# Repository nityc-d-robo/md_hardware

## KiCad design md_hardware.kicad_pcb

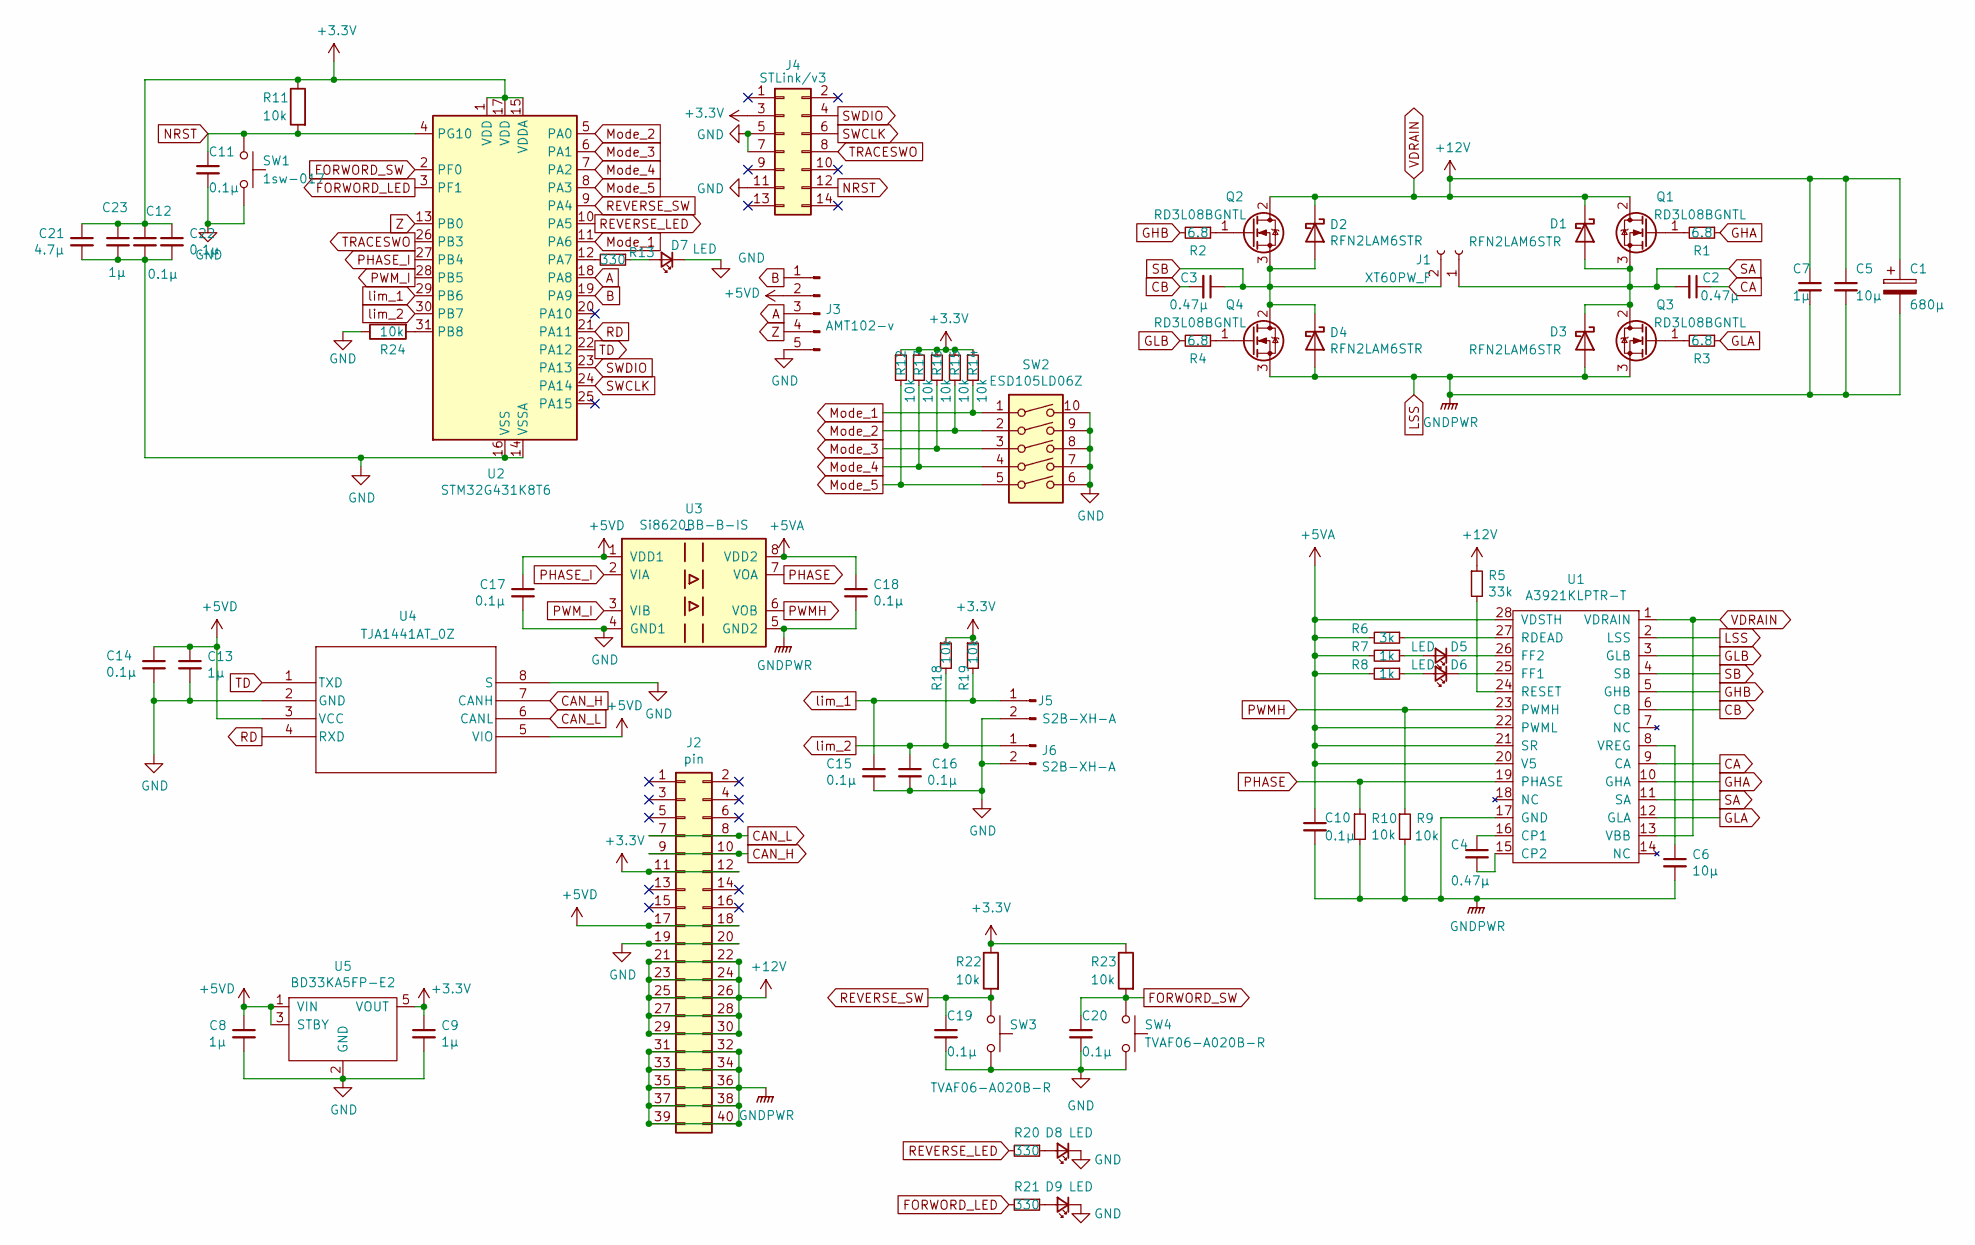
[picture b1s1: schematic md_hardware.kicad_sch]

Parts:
C1: 680µ; CP_Elec_10x12.6
C2, C3, C4: 0.47μ; C_0603_1608Metric_Pad1.08x0.95mm_HandSolder
C5, C6: 10μ; C_0603_1608Metric_Pad1.08x0.95mm_HandSolder
C7, C8, C9, C13, C23: 1μ; C_0603_1608Metric_Pad1.08x0.95mm_HandSolder
C10, C11, C12, C14, C15, C16, C17, C18, C19, C20, C22: 0.1μ; C_0603_1608Metric_Pad1.08x0.95mm_HandSolder
C21: 4.7μ; C_0603_1608Metric_Pad1.08x0.95mm_HandSolder
D1, D2, D3, D4: RFN2LAM6STR; D_SOD-128
D5, D6, D7, D8, D9: LED; LED_0603_1608Metric_Pad1.05x0.95mm_HandSolder
J1: XT60PW_F; XT60PW-F
J2: pin; PinHeader_2x20_P2.54mm_Horizontal
J3: AMT102-v; JST_XH_S5B-XH-A_1x05_P2.50mm_Horizontal
J4: STLink/v3; CONN14_3220-14_CNC
J5, J6: S2B-XH-A; JST_XH_S2B-XH-A_1x02_P2.50mm_Horizontal
Q1, Q2, Q3, Q4: RD3L08BGNTL; TO-252-2
R1, R2, R3, R4: 6.8; R_0603_1608Metric_Pad0.98x0.95mm_HandSolder
R5: 33k; R_0603_1608Metric_Pad0.98x0.95mm_HandSolder
R6: 3k; R_0603_1608Metric_Pad0.98x0.95mm_HandSolder
R7, R8: 1k; R_0603_1608Metric_Pad0.98x0.95mm_HandSolder
R9, R10, R11, R12, R14, R15, R16, R17, R18, R19, R22, R23, R24: 10k; R_0603_1608Metric_Pad0.98x0.95mm_HandSolder
R13, R20, R21: 330; R_0603_1608Metric_Pad0.98x0.95mm_HandSolder
SW1: 1sw-017; TVAF06-A020B-R
SW2: ESD105LD06Z; SW_DIP_SPSTx05_Slide_ESD105LD06Z_P2.54mm
SW3, SW4: TVAF06-A020B-R
U1: A3921KLPTR-T; TSSOP-28_4.4x9.7mm_P0.65mm
U2: STM32G431K8T6; LQFP-32_7x7mm_P0.8mm
U3: Si8620BB-B-IS; SOIC-8_3.9x4.9mm_P1.27mm
U4: TJA1441AT_0Z; SO8_SOT96-1_NXP
U5: BD33KA5FP-E2; SOT-23-5

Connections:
+3.3V: C9.1, C12.1, C21.1, C22.1, C23.1, J2.11, J2.12, J4.3, R11.1, R12.1, R14.1, R15.1, R16.1, R17.1, R18.1, R19.1, R22.1, R23.1, U2.1 (VDD), U2.15 (VDDA), U2.17 (VDD), U5.5 (VOUT)
+5VA: C10.1, C18.1, R6.2, R7.2, R8.2, U1.20 (V5), U1.21 (SR), U1.22 (PWML), U1.28 (VDSTH), U3.8 (VDD2)
+5VD: C8.1, C13.1, C14.1, C17.1, J2.17, J2.18, J3.2, U3.1 (VDD1), U4.3 (VCC), U4.5 (VIO), U5.1 (VIN), U5.3 (STBY)
A: J3.3, U2.18 (PA8)
B: J3.1, U2.19 (PA9)
CA: C2.1, U1.9 (CA)
CAN_H: J2.9, J2.10, U4.7 (CANH)
CAN_L: J2.7, J2.8, U4.6 (CANL)
CB: C3.2, U1.6 (CB)
FORWORD_LED: R21.2, U2.3 (PF1)
FORWORD_SW: C20.1, R23.2, SW4.1, U2.2 (PF0)
GHA: R1.1, U1.10 (GHA)
GHB: R2.2, U1.5 (GHB)
GLA: R3.1, U1.12 (GLA)
GLB: R4.2, U1.3 (GLB)
GND: C8.2, C9.2, C11.2, C12.2, C13.2, C14.2, C15.2, C16.2, C17.2, C19.2, C20.2, C21.2, C22.2, C23.2, D7.1 (K), D8.1 (K), D9.1 (K), J2.19, J2.20, J3.5, J4.5, J4.7, J4.11, J5.2, J6.2, R24.1, SW1.2, SW2.6, SW2.7, SW2.8, SW2.9, SW2.10, SW3.2, SW4.2, U2.14 (VSSA), U2.16 (VSS), U2.32 (VSS), U3.4 (GND1), U4.2 (GND), U4.8 (S), U5.2 (GND)
LSS: C1.2, C5.2, C6.2, C7.2, C10.2, C18.2, D3.2 (A), D4.2 (A), J2.31, J2.32, J2.33, J2.34, J2.35, J2.36, J2.37, J2.38, J2.39, J2.40, Q3.3 (S), Q4.3 (S), R9.2, R10.2, U1.2 (LSS), U1.17 (GND), U3.5 (GND2)
Mode_1: R14.2, SW2.1, U2.11 (PA6)
Mode_2: R15.2, SW2.2, U2.5 (PA0)
Mode_3: R16.2, SW2.3, U2.6 (PA1)
Mode_4: R17.2, SW2.4, U2.7 (PA2)
Mode_5: R12.2, SW2.5, U2.8 (PA3)
NRST: C11.1, J4.12, R11.2, SW1.1, U2.4 (PG10)
unnamed: D5.2 (A), R7.1
unnamed: D5.1 (K), U1.26 (FF2)
unnamed: D6.2 (A), R8.1
unnamed: D6.1 (K), U1.25 (FF1)
unnamed: D7.2 (A), R13.1
unnamed: D8.2 (A), R20.1
unnamed: D9.2 (A), R21.1
unnamed: Q1.1 (G), R1.2
unnamed: Q2.1 (G), R2.1
unnamed: Q3.1 (G), R3.2
unnamed: Q4.1 (G), R4.1
unnamed: C4.1, U1.16 (CP1)
unnamed: C4.2, U1.15 (CP2)
unnamed: R6.1, U1.27 (RDEAD)
unnamed: R5.2, U1.24 (RESET)
unnamed: C6.1, U1.8 (VREG)
unnamed: R13.2, U2.12 (PA7)
unnamed: R24.2, U2.31 (PB8)
PHASE: R10.1, U1.19 (PHASE), U3.7 (VOA)
PHASE_I: U2.27 (PB4), U3.2 (VIA)
PWMH: R9.1, U1.23 (PWMH), U3.6 (VOB)
PWM_I: U2.28 (PB5), U3.3 (VIB)
RD: U2.21 (PA11), U4.4 (RXD)
REVERSE_LED: R20.2, U2.10 (PA5)
REVERSE_SW: C19.1, R22.2, SW3.1, U2.9 (PA4)
SA: C2.2, D1.2 (A), D3.1 (K), J1.1, Q1.3 (S), Q3.2 (D), U1.11 (SA)
SB: C3.1, D2.2 (A), D4.1 (K), J1.2, Q2.3 (S), Q4.2 (D), U1.4 (SB)
SWCLK: J4.6, U2.24 (PA14)
SWDIO: J4.4, U2.23 (PA13)
TD: U2.22 (PA12), U4.1 (TXD)
TRACESWO: J4.8, U2.26 (PB3)
VDRAIN: C1.1, C5.1, C7.1, D1.1 (K), D2.1 (K), J2.21, J2.22, J2.23, J2.24, J2.25, J2.26, J2.27, J2.28, J2.29, J2.30, Q1.2 (D), Q2.2 (D), R5.1, U1.1 (VDRAIN), U1.13 (VBB)
Z: J3.4, U2.13 (PB0)
lim_1: C15.1, J5.1, R19.2, U2.29 (PB6)
lim_2: C16.1, J6.1, R18.2, U2.30 (PB7)

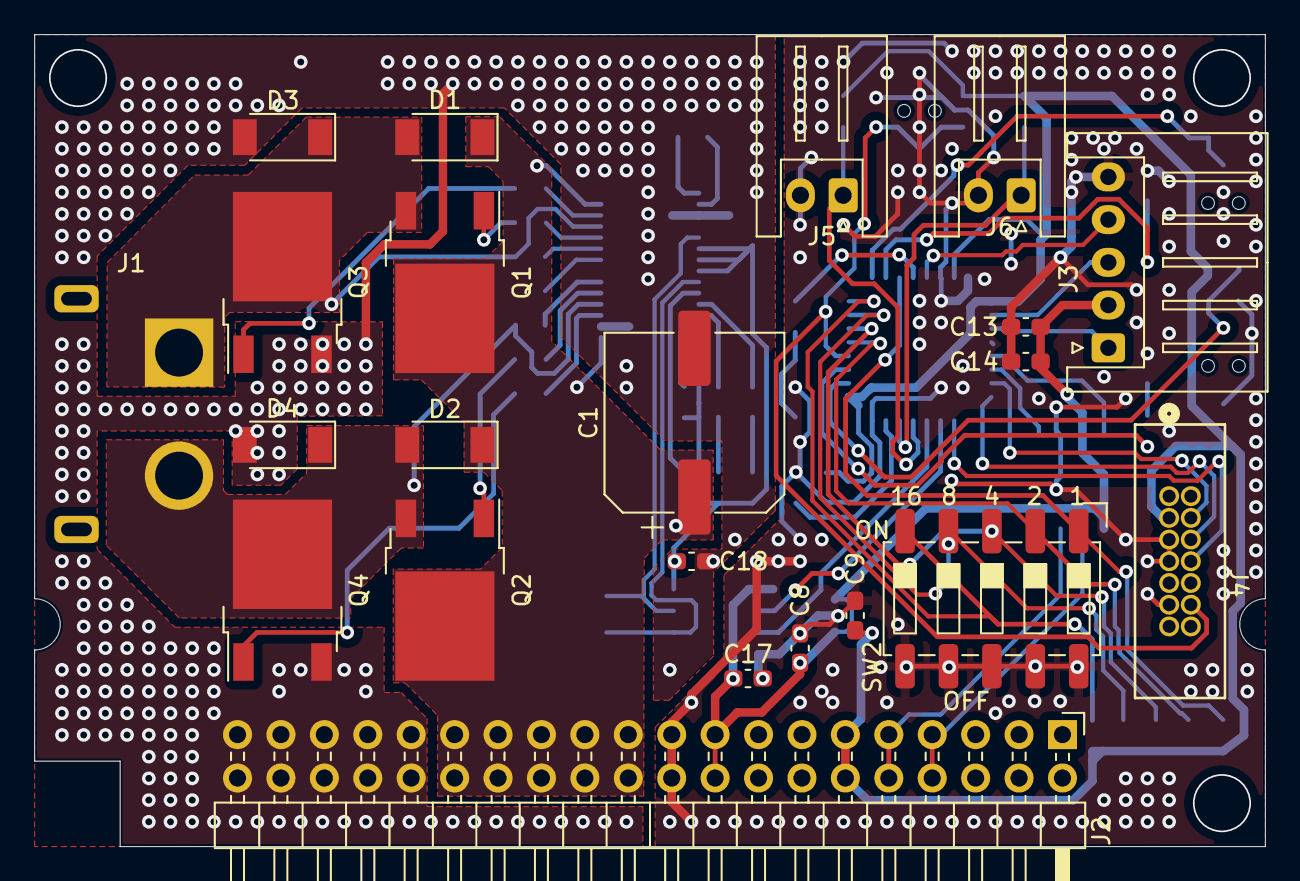
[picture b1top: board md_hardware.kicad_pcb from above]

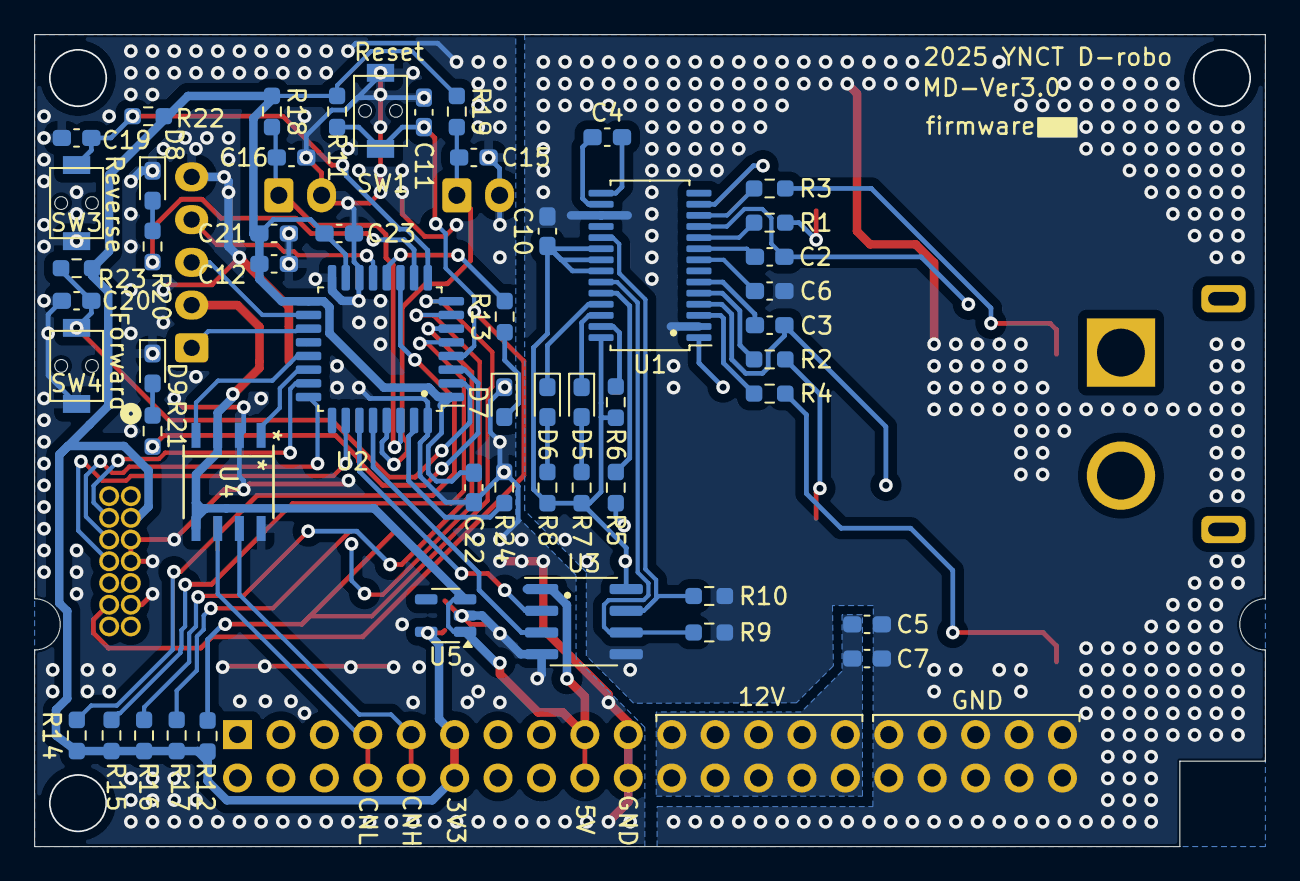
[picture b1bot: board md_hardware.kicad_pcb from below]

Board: 2 copper layers, 72.0 x 47.5 mm, 75 parts (53 on the bottom side), 58 nets.

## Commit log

2021-12-04 change libs
2021-12-04 change lib
2021-12-04 change paths
2021-12-04 change 3Ds
2021-12-17 adding datasheets to symbols
2021-12-18 change U2 Symbol
2021-12-18 added datasheets to symbols
2021-12-18 copy from Ver2.2
2021-12-19 add firmware memo zone
2022-01-13 adding current sensor
2022-01-22 complete figure
2022-01-22 connecting wire
2022-01-22 adjusting fill zone
2022-01-23 complete wiring
2022-01-23 complete without silk(add bipass capaciter
2022-01-24 complete silk
2022-01-24 change silk version
2022-08-15 add gitignore
2022-08-15 none
2025-02-23 change STM32f303 pin arrangement, delete changeover switch, add Forward,Reverse SW
2025-02-24 ビアや配線を細かく調整
2025-03-08 Updated version and date/time silks
2025-04-22 STM32G491KEU6に改修 STLinkコネクタを表面に修正
2025-05-03 fix st-link v3 footprint ,change from f303 to g431
2025-08-10 Swap PWM pin and phase pin, and change ID SW.
